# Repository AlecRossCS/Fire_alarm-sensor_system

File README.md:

# Fire_alarm-sensor_system Hardware
This was a capstone design project at the University of Virginia. 
the full report can be found here: [capstone thesis report](ECE_4440-4991-Design-Project-Final_Report.pdf)
## Design elements
The initial goal of this project is the problem: How can someone tell if a barn, fields, or their forests are on fire. This system is a proof of concept for a fire alarm sensor system deployable close to human infrastructure, as opposed to in remote locations. This system communicates over wifi to trigger an alarm, as well as provide air quality, humidity, and temperature data. Other communication systems were considered, particularly LoRA, but they are more suited to remote locations deep in forests or other areas for wild fire protection, rather than close to or on managed properties. The design is meant to be fairly simple, as to allow a price point of at most $100 per device but through good supply chain optimization it could fall to as low as $40. The device is battery powered, as most fire alarms, but instead of it being for backup it powers main operation and sends alerts when the battery is low. 

## Electrical Design
The primary elements of consideration here was low power usage. So the device is designed to run from a single 18650 lithium battery, although a 2P 18650 system would run double the time, with full recharging built in. this meant that to maintain efficiency, the device operation voltage should be 3.3V. this happened via a low dropout Linear regulator, although finished designs and ultra power efficient devices should use a buck-boost, or sepic configuration switching supplies to increase power effiency into the 90-99% power efficient ranges. The sensors themselves were chosen to be compatible with 3.3V, as well as common protocols to allow easy communication with a microcontroller, which in this case I2C devices were chosen, as the other most common protocol SPI is less space and pin efficient and the benefit of higher data transfer rates are not needed. The gas sensor was the most sensitive component of assembly, a ZMOD line chip, and required working with the assembler to gurantee that it would not be damaged in the assembly process. 

## Budget Bill of Materials Costs
The bill of materials (BOM) was monitored and considered through out. several optimizations compared to other projects played out. Firstly, all parts ordered were SMD which, in general reduces the space requirements, which reduce manufacturing and assembly costs, as well as being generally cheaper than through hole components. another point of consideration, it is also cheaper to buy larger quantities of basic passive components than to buy them in the singles, so generally parts were bought in the tens or hundreds when cheaper than 3 or 4.

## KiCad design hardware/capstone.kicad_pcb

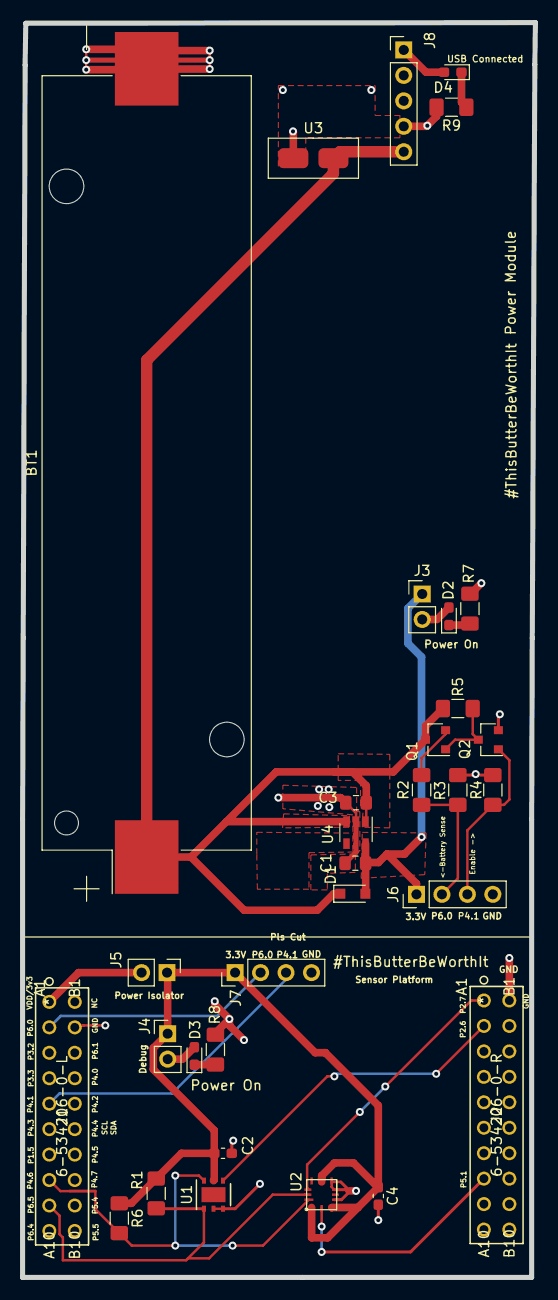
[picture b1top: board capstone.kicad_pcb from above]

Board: 2 copper layers, 51.2 x 125.2 mm, 32 parts (0 on the bottom side), 19 nets.

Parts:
BT1: Battery_Cell; BatteryHolder_Keystone_1042_1x18650
C1, C3: 1 uF; C_0805_2012Metric_Pad1.15x1.40mm_HandSolder
C2: 0.1uF; C_0603_1608Metric_Pad1.05x0.95mm_HandSolder
C4: 0.1 uF; C_0603_1608Metric_Pad1.05x0.95mm_HandSolder
D1: D_Schottky; D_SOD-323_HandSoldering
D2, D3, D4: LED; LED_0603_1608Metric_Pad1.05x0.95mm_HandSolder
J1: 6-534206-0-L; 6-534206-0
J2: 6-534206-0-R; 6-534206-0
J3, J4, J5: Conn_01x02; PinHeader_1x02_P2.54mm_Vertical
J6, J7: Conn_01x04; PinHeader_1x04_P2.54mm_Vertical
J8: Conn_01x05; PinHeader_1x05_P2.54mm_Vertical
Q1: NTR5105PT1G; SOT-23
Q2: BSS138L; SOT-23
R1, R6: 10K; R_1206_3216Metric_Pad1.42x1.75mm_HandSolder
R2, R3, R4, R5: 100K; R_1206_3216Metric_Pad1.42x1.75mm_HandSolder
R7, R8, R9: 500; R_1206_3216Metric_Pad1.42x1.75mm_HandSolder
U1: HDC2080; Texas_PWSON-N6
U2: ZMOD4510AI1V; ZMOD4510
U3: WireConnect; Wire_Connector
U4: TLV75509PDBV; SOT-23-5

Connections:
/GND: BT1.2, C1.2, C2.2, C3.2, C4.2, J1.B2, J2.B1, J6.4, J7.4, J8.4, Q2.2, R3.2, R4.2, R7.2, R8.2, R9.2, U1.2, U1.3, U2.6, U2.7, U2.9, U3.1, U4.2
/SCL: J1.A8, R6.2, U1.6, U2.1
/SDA: J1.A9, R1.2, U1.1, U2.2
/Sheet5F7BACC0/Battery_Indicator/Pull_up: Q1.1, Q2.3, R5.2
/Sheet5F7BACC0/UnReg_VDD: BT1.1, C3.1, D1.1, J8.5, Q1.3, R5.1, U3.2, U4.1, U4.3
/VDD: C1.1, C2.1, C4.1, D1.2, J3.1, J4.1, J5.1, J6.1, J7.1, R1.1, R6.1, U1.5, U2.5, U2.10, U2.12, U4.5
unnamed: D2.1, R7.1
unnamed: D2.2, J3.2
unnamed: D3.1, R8.1
unnamed: D3.2, J4.2
unnamed: D4.1, R9.1
unnamed: D4.2, J8.1
unnamed: J1.A1, J5.2
unnamed: Q1.2, R2.2
P2.6: J2.A2, U1.4
P2.7: J2.A1, U2.3
P4.1: J1.A5, J6.3, J7.3, Q2.1, R4.1
P5.1: J2.A8, U2.11
P6.0A: J1.A2, J6.2, J7.2, R2.1, R3.1

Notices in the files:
parts and their libraries:
Copyright 2016 Accelerated Designs. All rights reserved.
